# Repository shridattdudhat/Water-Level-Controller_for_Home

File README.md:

# DIY_WaterLevel_For_Home
Simple Water Level Controller Using Arduino
Water Level
Automatic detects Water level of Tank and turn on and off motor according to it
https://shridatt.github.io
modified 27 Oct 2019 Diwali
by Shridatt Dudhat
           _            _
           |         G  |  => H
           |            |
           |            |
           |         R  |  => L
           |            |
           |            |
           \_________B__/  => GND
This code is in the public domain.
http://shridattdudhat.github.io

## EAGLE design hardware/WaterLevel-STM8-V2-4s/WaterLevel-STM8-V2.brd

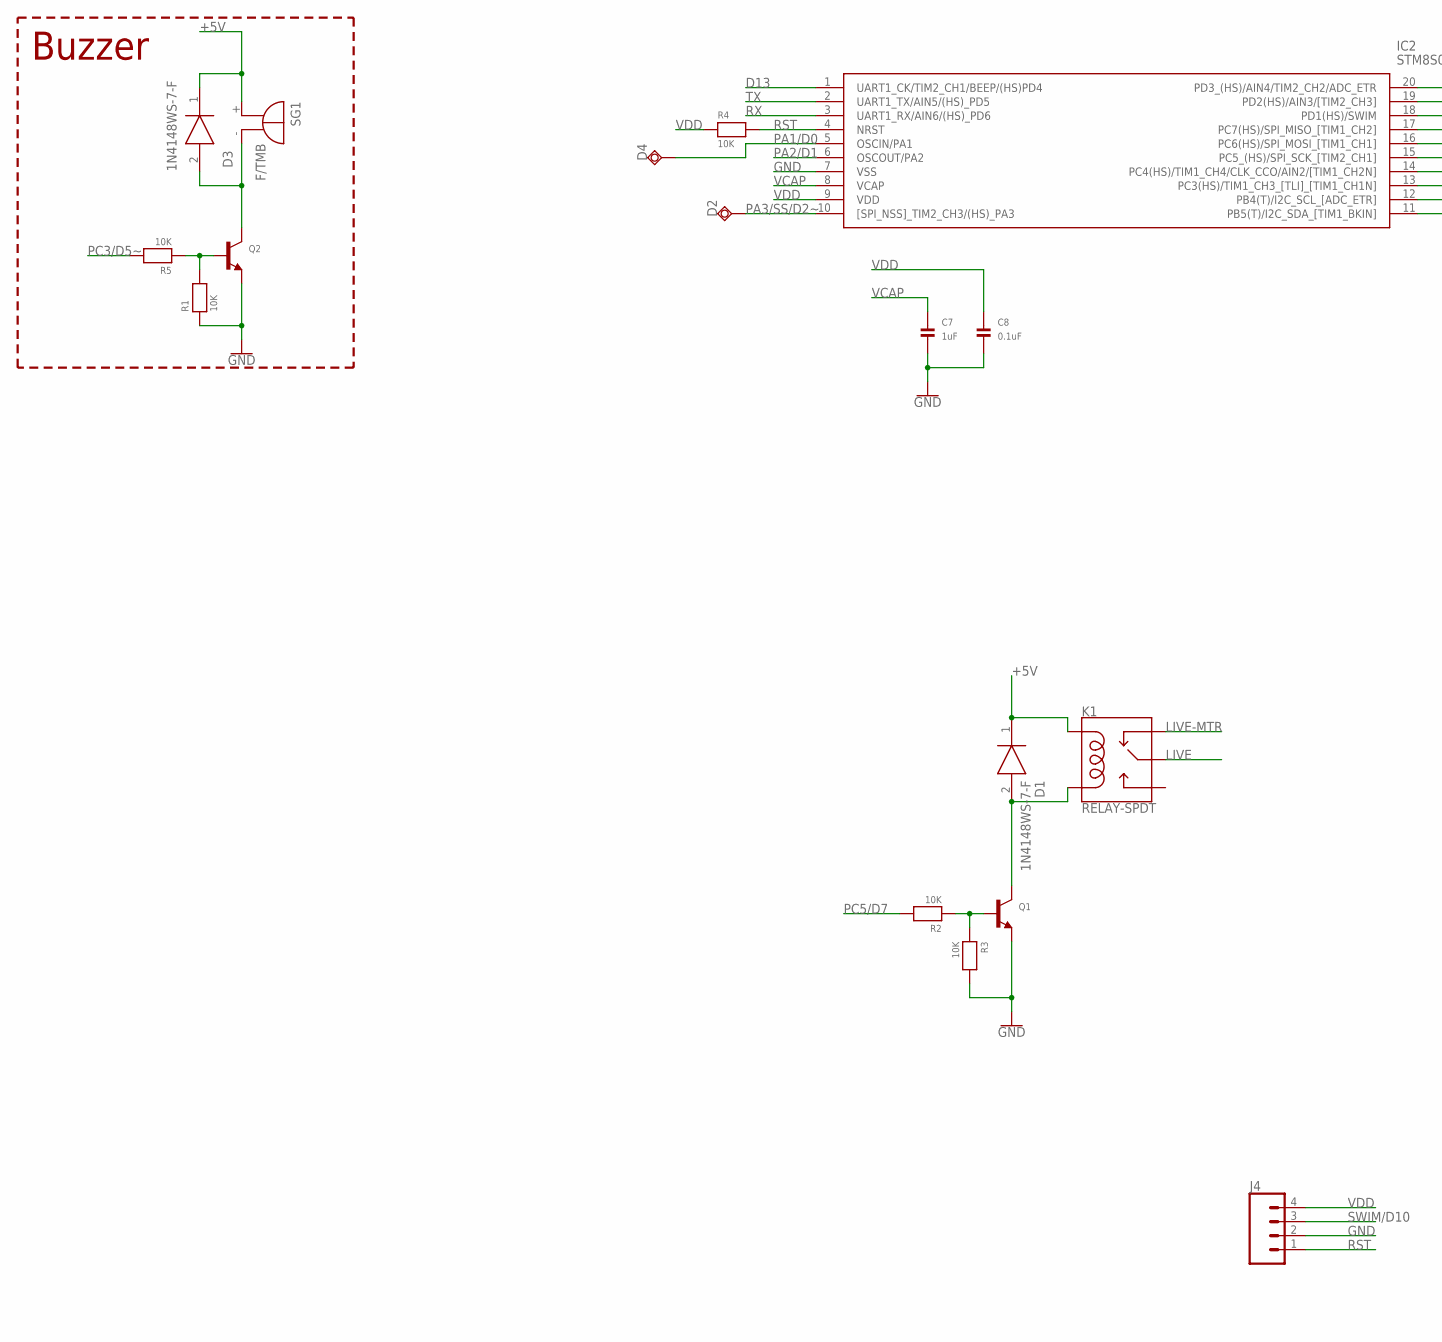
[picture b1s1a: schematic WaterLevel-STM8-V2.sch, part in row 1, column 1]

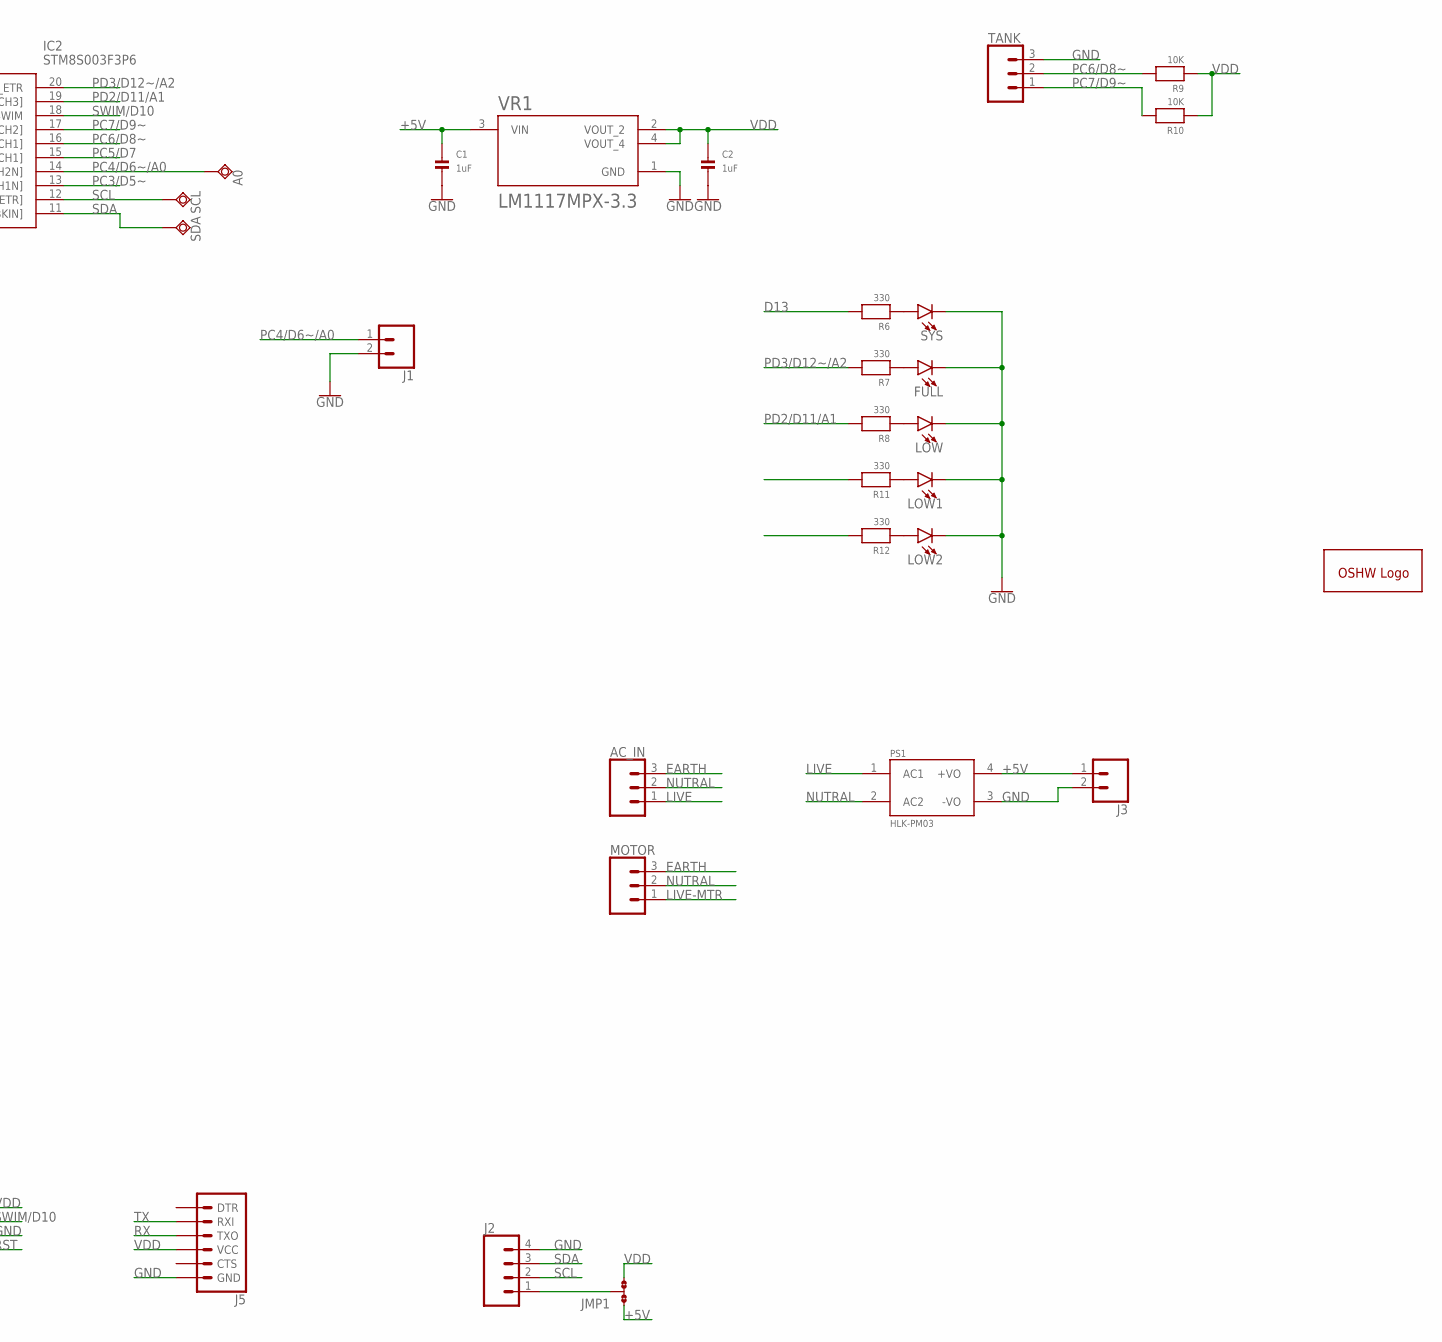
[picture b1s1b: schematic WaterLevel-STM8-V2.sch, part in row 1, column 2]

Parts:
A0: TPSQTP20R; TP20R
AC_IN: SCREW-CONN_03-SCREW-5MM; SCREWTERMINAL-5MM-3
C1, C2, C7: 1uF; C0805
C8: 0.1uF; C0805
D1, D3: 1N4148WS-7-F; SOD2513X120N
D2, D4: TPSQTP20R; TP20R
FULL: LED-5MM-REC5MM; LED_5MM
GOLD_ORB_SM1: OSHWLOGOLOGO16MM; OSHW_16MM
IC2: STM8S003F3P6; SOP65P640X120-20N
J1, J3: 2PIN-2.54MM-POLARPOLAR; MOLEX-1X2
J2, J4: CONN_04PTH; 1X04
J5: 6_PIN_SERIAL_TARGETSILK; 6_PIN_SERIAL_TARGET_SIDE_W_SILK
JMP1: JMP-3-NO
K1: RELAY-SPDT; RELAY_G5LE
LOW, LOW1, LOW2: LED-5MM-REC5MM; LED_5MM
MOTOR: SCREW-CONN_03-SCREW-5MM; SCREWTERMINAL-5MM-3
PS1: HLK-PM03; CONV_HLK-PM03
Q1, Q2: TRANSISTOR_NPNWIDE; SOT23-WIDE
R1, R2, R3, R4, R5, R9, R10: 10K; R0805
R6, R7, R8, R11, R12: 330; R0805
SCL: TPSQTP20R; TP20R
SDA: TPSQTP20R; TP20R
SG1: F/TMB
SYS: LED-5MM-REC5MM; LED_5MM
TANK: SCREW-CONN_03-SCREW-5MM; SCREWTERMINAL-5MM-3
VR1: LM1117MPX-3.3; VREG_LM1117MPX-3.3

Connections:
+5V: C1.1, D1.1 (K), D3.1 (K), J3.1, JMP1.1, K1.2 (COIL1), PS1.4 (+VO), SG1.+, VR1.3 (VIN)
D13: IC2.1 (UART1_CK/TIM2_CH1/BEEP/(HS)PD4), R6.2
EARTH: AC_IN.3, MOTOR.3
GND: C1.2, C2.2, C7.2, C8.2, FULL.K (C), IC2.7 (VSS), J1.2, J2.4, J3.2, J4.2, J5.P$6 (GND), LOW.K (C), LOW1.K (C), LOW2.K (C), PS1.3 (-VO), Q1.2 (E), Q2.2 (E), R1.1, R3.2, SYS.K (C), TANK.3, VR1.1 (GND)
LIVE: AC_IN.1, K1.1 (MAIN), PS1.1 (AC1)
LIVE-MTR: K1.4 (NC), MOTOR.1
unnamed: R6.1, SYS.A
unnamed: D1.2 (A), K1.5 (COIL2), Q1.3 (C)
unnamed: Q1.1 (B), R2.1, R3.1
unnamed: D3.2 (A), Q2.3 (C), SG1.-
unnamed: Q2.1 (B), R1.2, R5.1
unnamed: FULL.A, R7.1
unnamed: LOW.A, R8.1
unnamed: J2.1, JMP1.2
unnamed: LOW1.A, R11.1
unnamed: LOW2.A, R12.1
NUTRAL: AC_IN.2, MOTOR.2, PS1.2 (AC2)
PA1/D0: D4.TP, IC2.5 (OSCIN/PA1)
PA2/D1: IC2.6 (OSCOUT/PA2)
PA3/SS/D2~: D2.TP, IC2.10 ([SPI_NSS]_TIM2_CH3/(HS)_PA3)
PC3/D5~: IC2.13 (PC3(HS)/TIM1_CH3_[TLI]_[TIM1_CH1N]), R5.2
PC4/D6~/A0: A0.TP, IC2.14 (PC4(HS)/TIM1_CH4/CLK_CCO/AIN2/[TIM1_CH2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), J1.1
PC5/D7: IC2.15 (PC5_(HS)/SPI_SCK_[TIM2_CH1]), R2.2
PC6/D8~: IC2.16 (PC6(HS)/SPI_MOSI_[TIM1_CH1]), R9.2, TANK.2
PC7/D9~: IC2.17 (PC7(HS)/SPI_MISO_[TIM1_CH2]), R10.2, TANK.1
PD2/D11/A1: IC2.19 (PD2(HS)/AIN3/[TIM2_CH3]), R8.2
PD3/D12~/A2: IC2.20 (PD3_(HS)/AIN4/TIM2_CH2/ADC_ETR), R7.2
RST: IC2.4 (NRST), J4.1, R4.2
RX: IC2.3 (UART1_RX/AIN6/(HS)_PD6), J5.P$2 (TXO)
SCL: IC2.12 (PB4(T)/I2C_SCL_[ADC_ETR]), J2.2, SCL.TP
SDA: IC2.11 (PB5(T)/I2C_SDA_[TIM1_BKIN]), J2.3, SDA.TP
SWIM/D10: IC2.18 (PD1(HS)/SWIM), J4.3
TX: IC2.2 (UART1_TX/AIN5/(HS)_PD5), J5.P$3 (RXI)
VCAP: C7.1, IC2.8 (VCAP)
VDD: C2.1, C8.1, IC2.9 (VDD), J4.4, J5.P$4 (VCC), JMP1.3, R4.1, R9.1, R10.1, VR1.2 (VOUT_2), VR1.4 (VOUT_4)

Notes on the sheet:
Buzzer

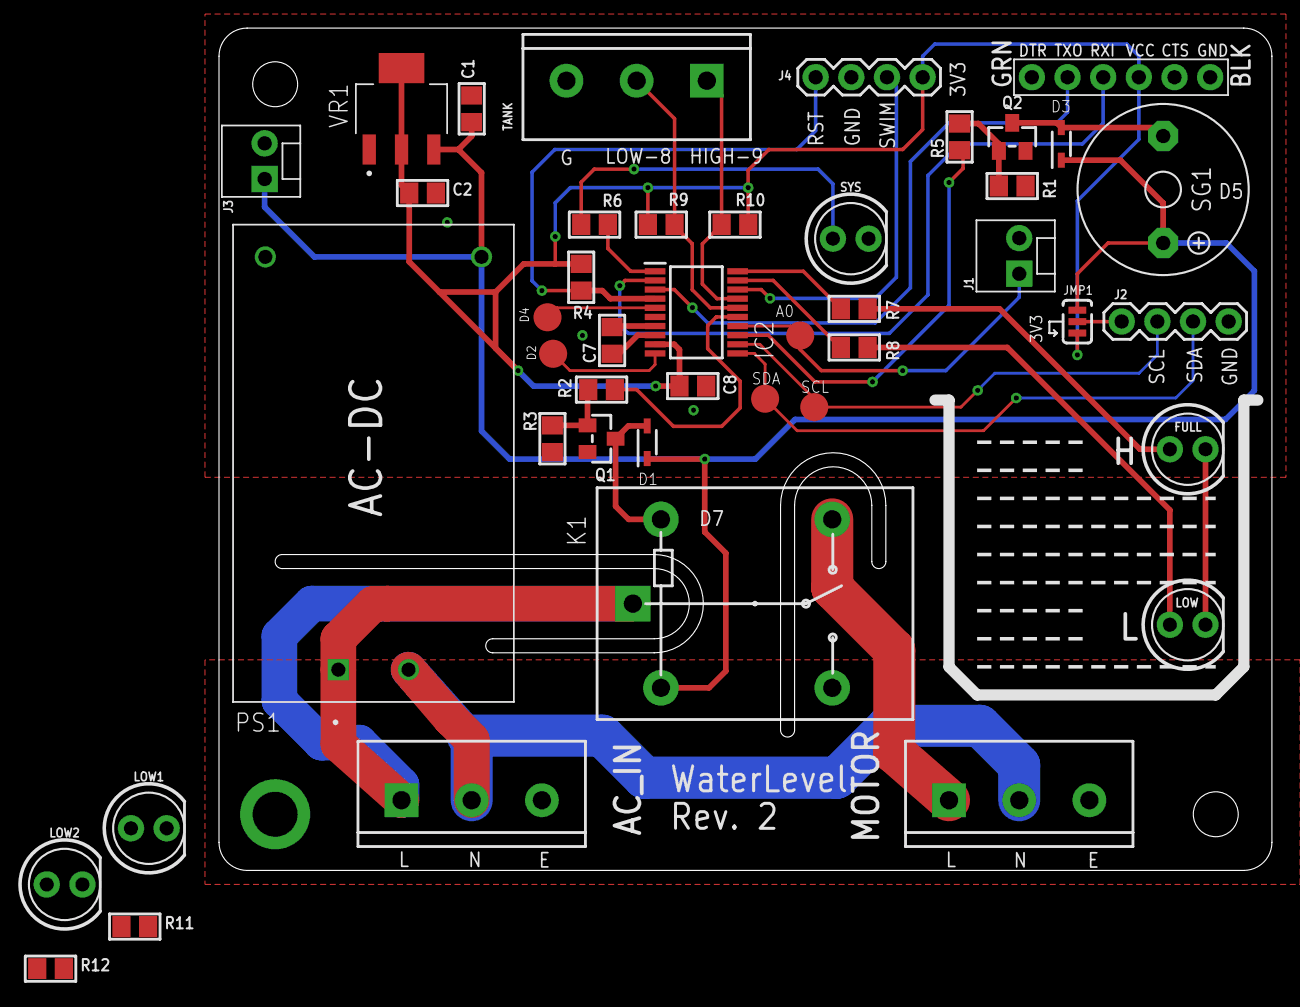
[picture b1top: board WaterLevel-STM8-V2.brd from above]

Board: 2 copper layers, 75.0 x 60.0 mm, 45 parts (1 on the bottom side), 34 nets.

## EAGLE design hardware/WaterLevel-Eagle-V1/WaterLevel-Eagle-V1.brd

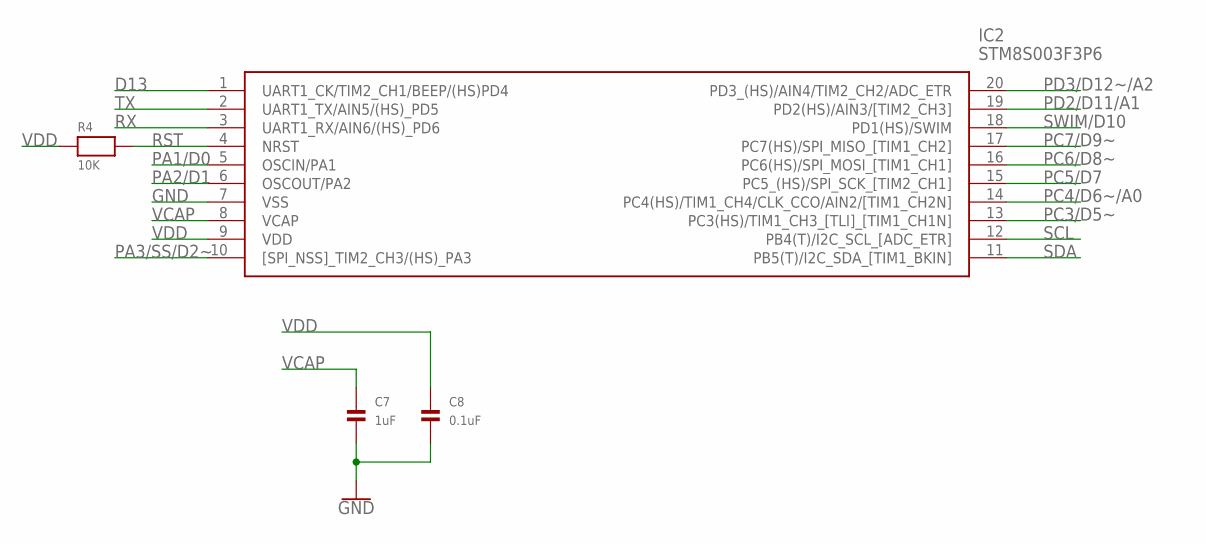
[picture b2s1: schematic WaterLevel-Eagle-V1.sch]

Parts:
C7: 1uF; C0805
C8: 0.1uF; C0805
IC2: STM8S003F3P6; SOP65P640X120-20N
R4: 10K; R0805

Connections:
D13: IC2.1 (UART1_CK/TIM2_CH1/BEEP/(HS)PD4)
GND: C7.2, C8.2, IC2.7 (VSS)
PA1/D0: IC2.5 (OSCIN/PA1)
PA2/D1: IC2.6 (OSCOUT/PA2)
PA3/SS/D2~: IC2.10 ([SPI_NSS]_TIM2_CH3/(HS)_PA3)
PC3/D5~: IC2.13 (PC3(HS)/TIM1_CH3_[TLI]_[TIM1_CH1N])
PC4/D6~/A0: IC2.14 (PC4(HS)/TIM1_CH4/CLK_CCO/AIN2/[TIM1_CH2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)
PC5/D7: IC2.15 (PC5_(HS)/SPI_SCK_[TIM2_CH1])
PC6/D8~: IC2.16 (PC6(HS)/SPI_MOSI_[TIM1_CH1])
PC7/D9~: IC2.17 (PC7(HS)/SPI_MISO_[TIM1_CH2])
PD2/D11/A1: IC2.19 (PD2(HS)/AIN3/[TIM2_CH3])
PD3/D12~/A2: IC2.20 (PD3_(HS)/AIN4/TIM2_CH2/ADC_ETR)
RST: IC2.4 (NRST), R4.2
RX: IC2.3 (UART1_RX/AIN6/(HS)_PD6)
SCL: IC2.12 (PB4(T)/I2C_SCL_[ADC_ETR])
SDA: IC2.11 (PB5(T)/I2C_SDA_[TIM1_BKIN])
SWIM/D10: IC2.18 (PD1(HS)/SWIM)
TX: IC2.2 (UART1_TX/AIN5/(HS)_PD5)
VCAP: C7.1, IC2.8 (VCAP)
VDD: C8.1, IC2.9 (VDD), R4.1

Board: 2 copper layers, 4 parts (0 on the bottom side), 4 nets, no tracks yet.

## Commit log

2019-02-10 Create WaterLevel.ino
    Simple Code for water level Test
2019-02-10 Update WaterLevel.ino
    commnet added
2019-12-03 motorFlag added to avoid false trigger of motor ON
2019-12-29 Motor State error resolved
2019-12-29 interval change
2020-09-07 hardware for waterlevel controller
2020-09-20 #1 component placement in the PCB
2020-09-20 #1 Eagle Project renamed
2020-09-26 Set theme jekyll-theme-hacker
2020-09-26 #1 New PCB update
2020-10-01 Added I2C connector and Manual Switch to the board
2020-10-04 #1 New Gerber Generation with Manual Switch and I2C connector for other sensors
2020-10-08 V2 with 4Sensor prob
2021-07-10 Create WaterLevel-STM8-V1.s##
2021-07-27 Create LICENSE

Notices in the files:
parts and their libraries:
SparkFun-PowerSymbols: Licensing: Creative Commons ShareAlike 4.0 International - https://creativecommons.org/licenses/by-sa/4.0
PatternAgents-ProtoPads: License : http://creativecommons.org/licenses/by-sa/4.0
(Creative Commons 4.0)
